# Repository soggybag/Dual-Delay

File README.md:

# Dual Delay (working name)

Two PT2399 delay lines whose repeats can feed themselves, each other, or a blend of both. Idea stage (2026-10-25).

- **Idea and design plan:** [docs/Ideas.md](docs/Ideas.md)
- **Sibling project:** `../Loop Echo/` (single PT2399 + effects loop in the feedback). The delay block, limiter, LFO and mixer are reused from it (its PT2399 network comes from the user's Small Time, 2022).

- **Schematic:** [docs/DualDelay_schematic.pdf](docs/DualDelay_schematic.pdf), generated by `scripts/build_dualdelay.py` (`DualDelay.kicad_sch`). ERC 0. Rev 1.0.
- **Board:** `DualDelay.kicad_pcb`, from `scripts/buildpcb_dualdelay.py` (don't re-run it after editing the board in KiCad).

**Panel (1590BB landscape):** TIME 1, TIME 2, MIX over FB 1, TWIST, FB 2; SERIES toggle; status LED; one footswitch. Internal trims: RATE, DEPTH (LFO on line 2), FB MAX 1 / 2.

**Status:** **v1.0 SMD (2026-10-25)**, to be ordered as a prototype together with Loop Echo (not breadboarded). ERC 0. JLC basic parts except the two PT2399s. One AMS1117-5.0 per PT2399, kept apart on the board; FB MAX trims. Board `DualDelay.kicad_pcb`: 1590BB landscape, 100 × 83.5 mm, jacks on the top wall (OUT · DC · IN). Details: the v1.0 section of [docs/Ideas.md](docs/Ideas.md). **Fab files (2026-10-26, after the re-route):** `production/` (gitignored): `DualDelay.zip` (Gerbers + drill, slots included), `bom.csv` + `positions.csv` (105 SMD placements, top side, 28 lines, all LCSC), `DualDelay_hand_solder.csv`. In JLC's preview check U1 / U2 (PT2399) and U7 / U8 (SOT-223) rotation; the op-amps carry FT Rotation Offset 270. Drilling: [enclosure/README.md](enclosure/README.md). Routed 2026-10-26 (re-route: supply nets +9V / GND / V5_1 / V5_2 / VB / D1-A at 0.4 mm, signals 0.25 mm, 99 vias; C32 GND pad solid). Board DRC: 0 errors / 0 unconnected, parity clean, silk pass done 2026-10-26 (Gerbers regenerated): the only warnings left are the jack outlines past the top edge and D6's LED ring near the notch (by design), and four references touching a part outline (C13, C20, C28, C30). v0.2 breadboard schematic and its [Breadboard Plan](docs/Breadboard%20Plan.md) kept for reference (`scripts/build_dualdelay_v0.2.py`).

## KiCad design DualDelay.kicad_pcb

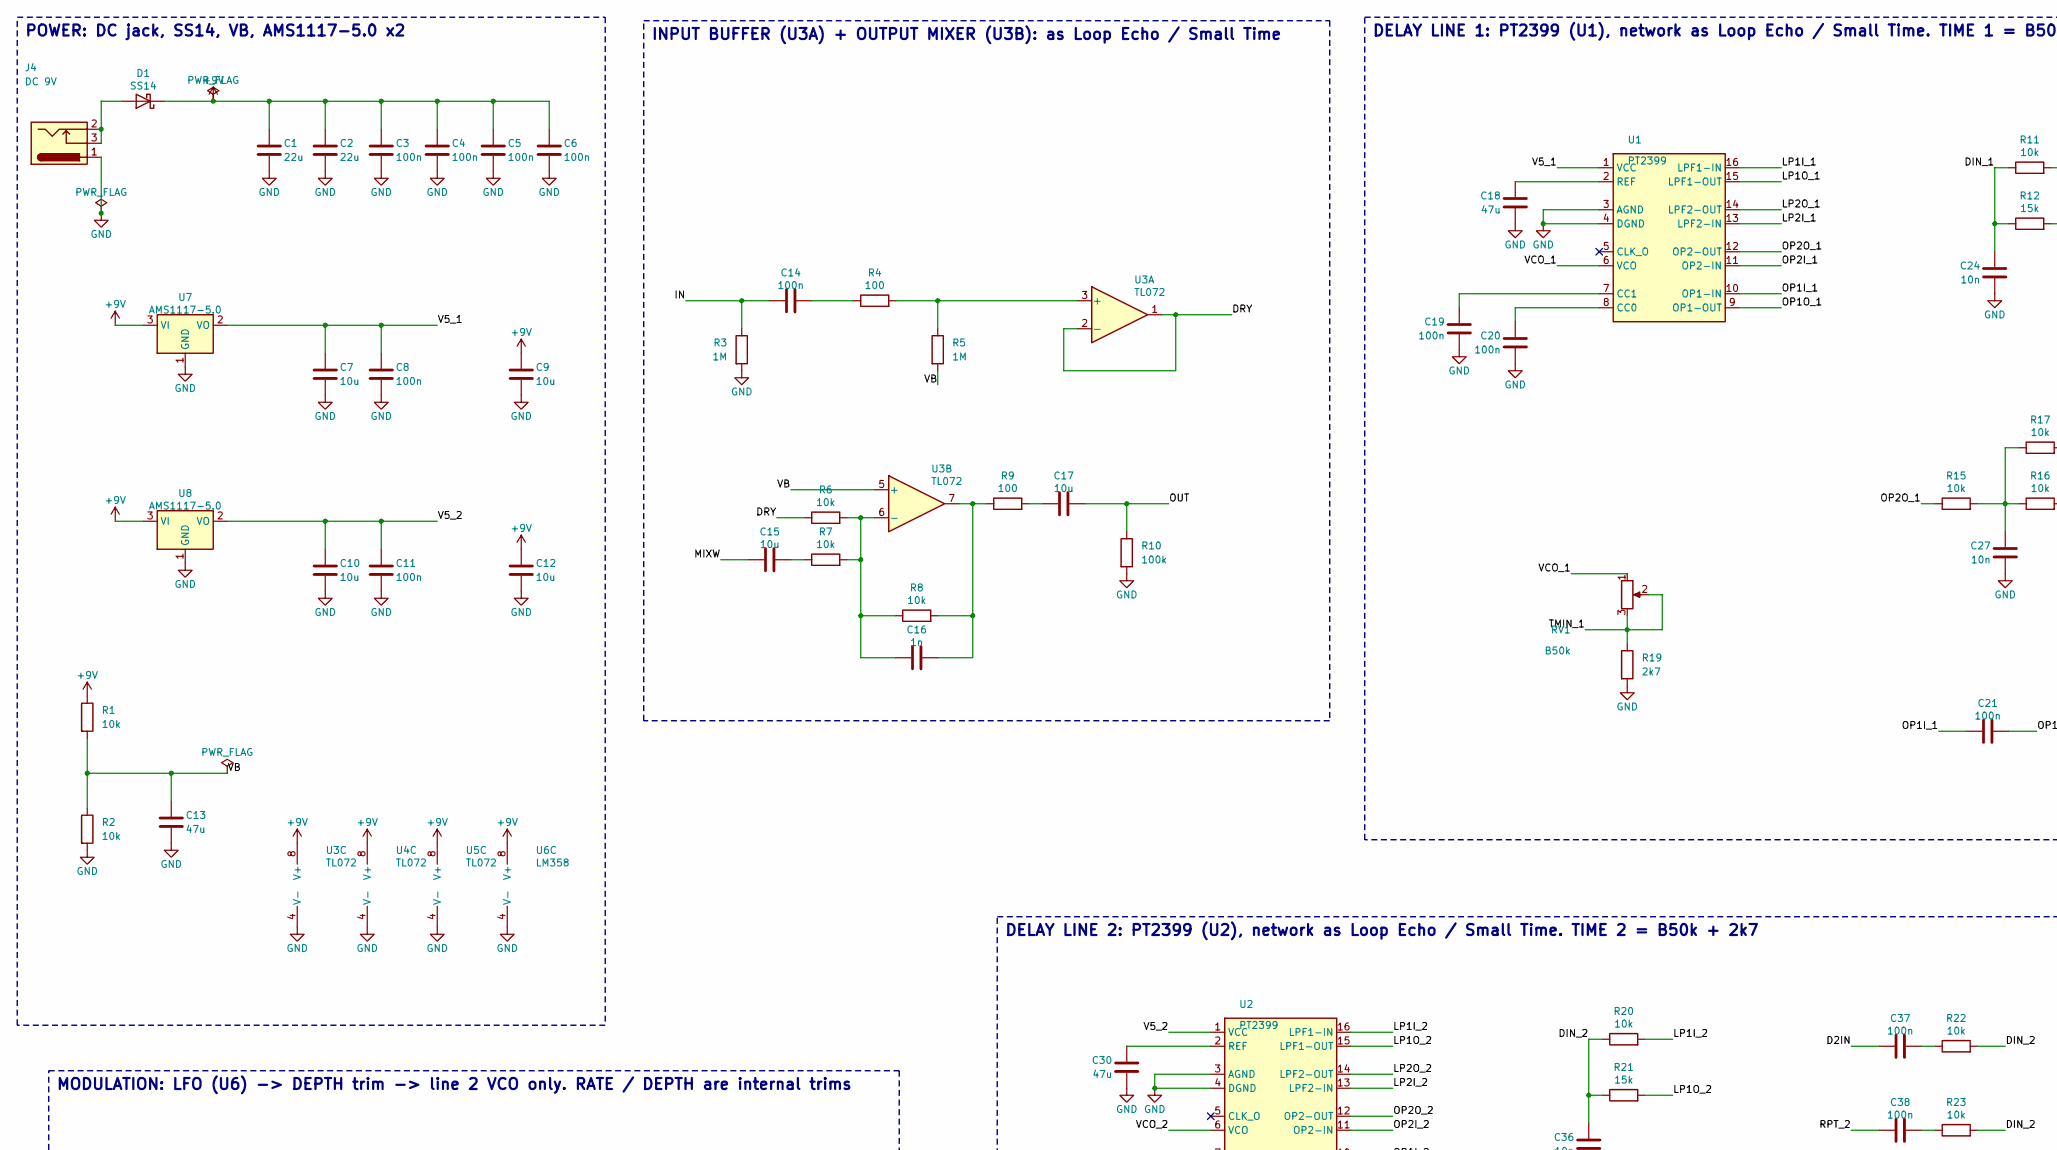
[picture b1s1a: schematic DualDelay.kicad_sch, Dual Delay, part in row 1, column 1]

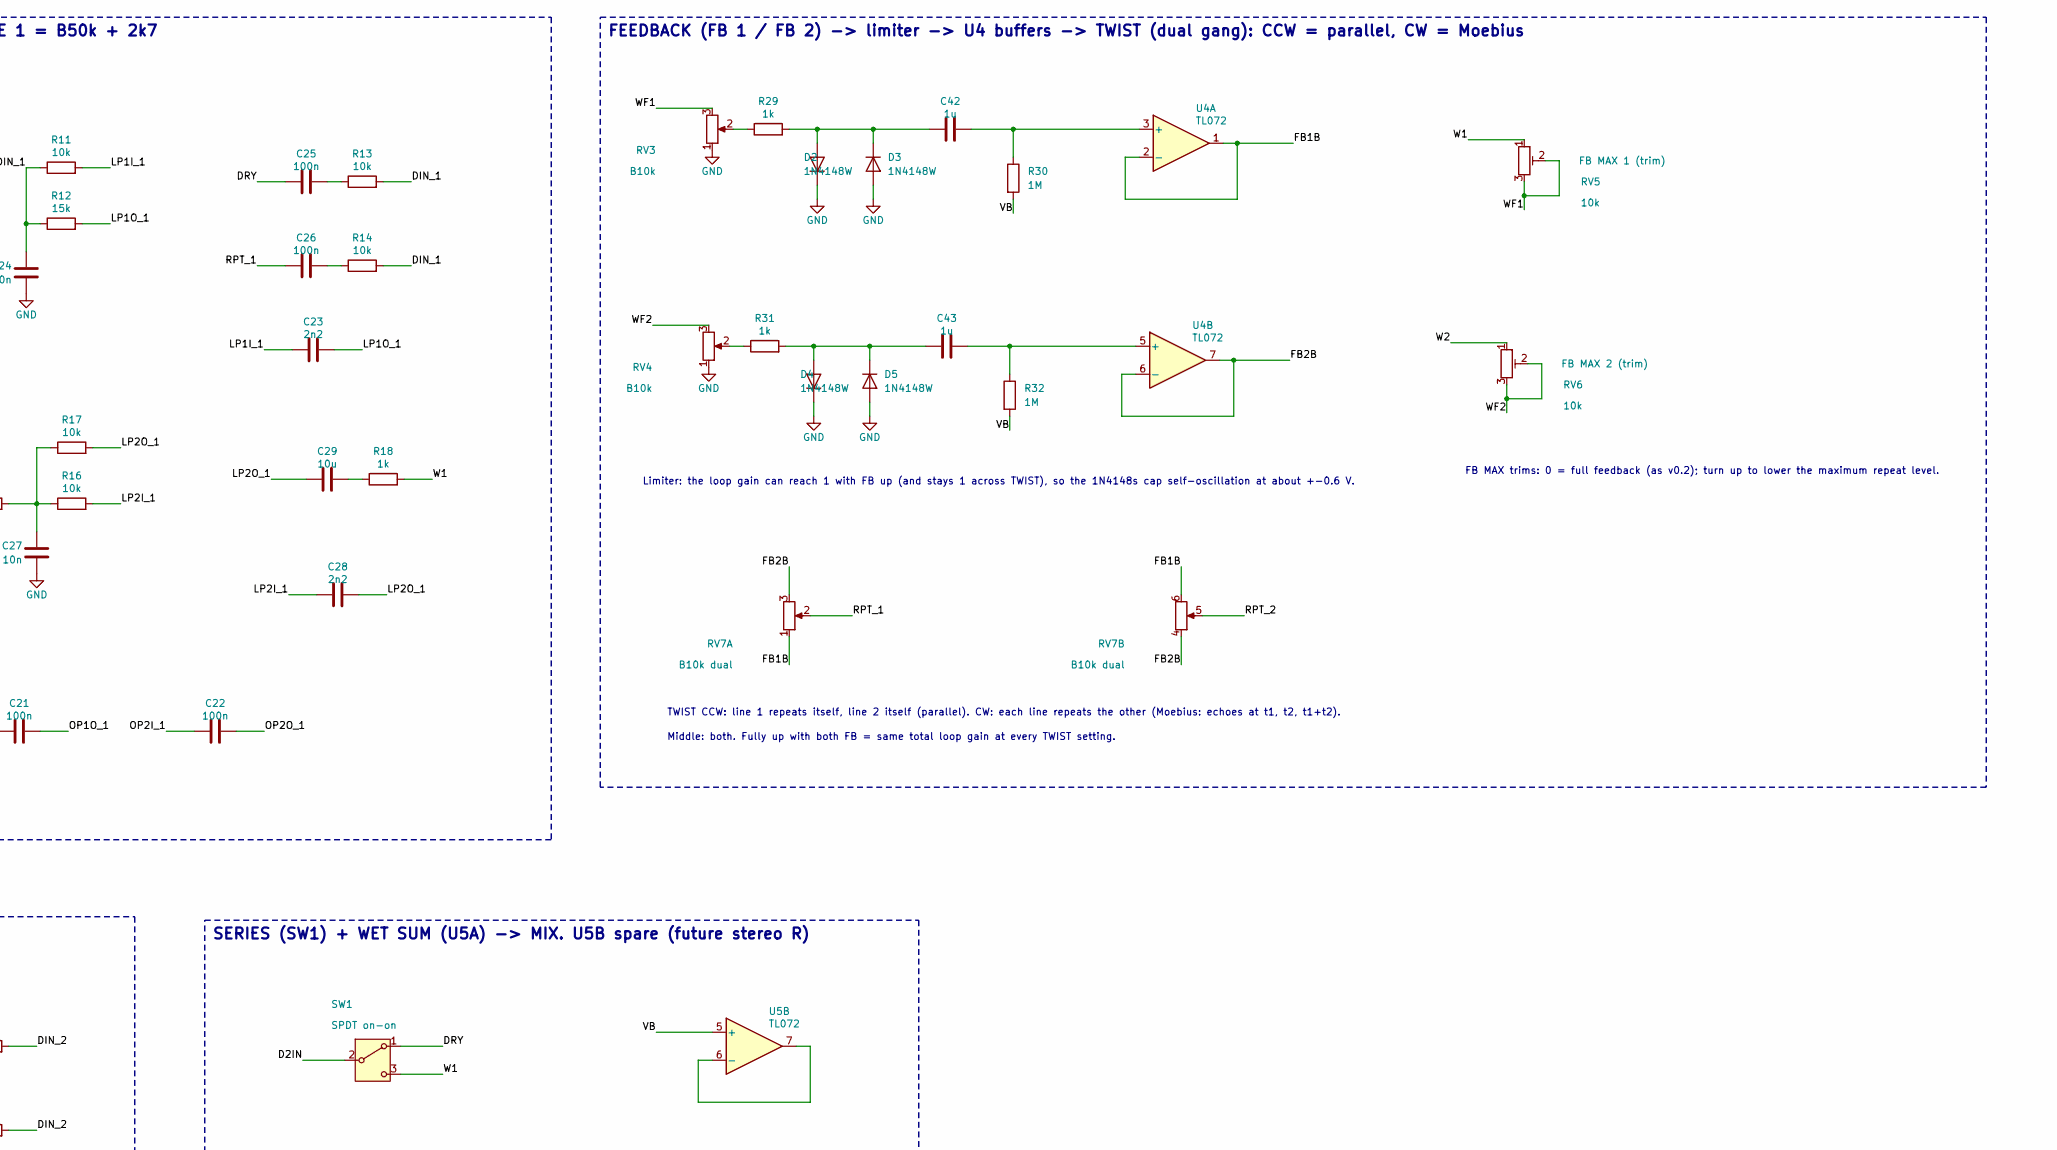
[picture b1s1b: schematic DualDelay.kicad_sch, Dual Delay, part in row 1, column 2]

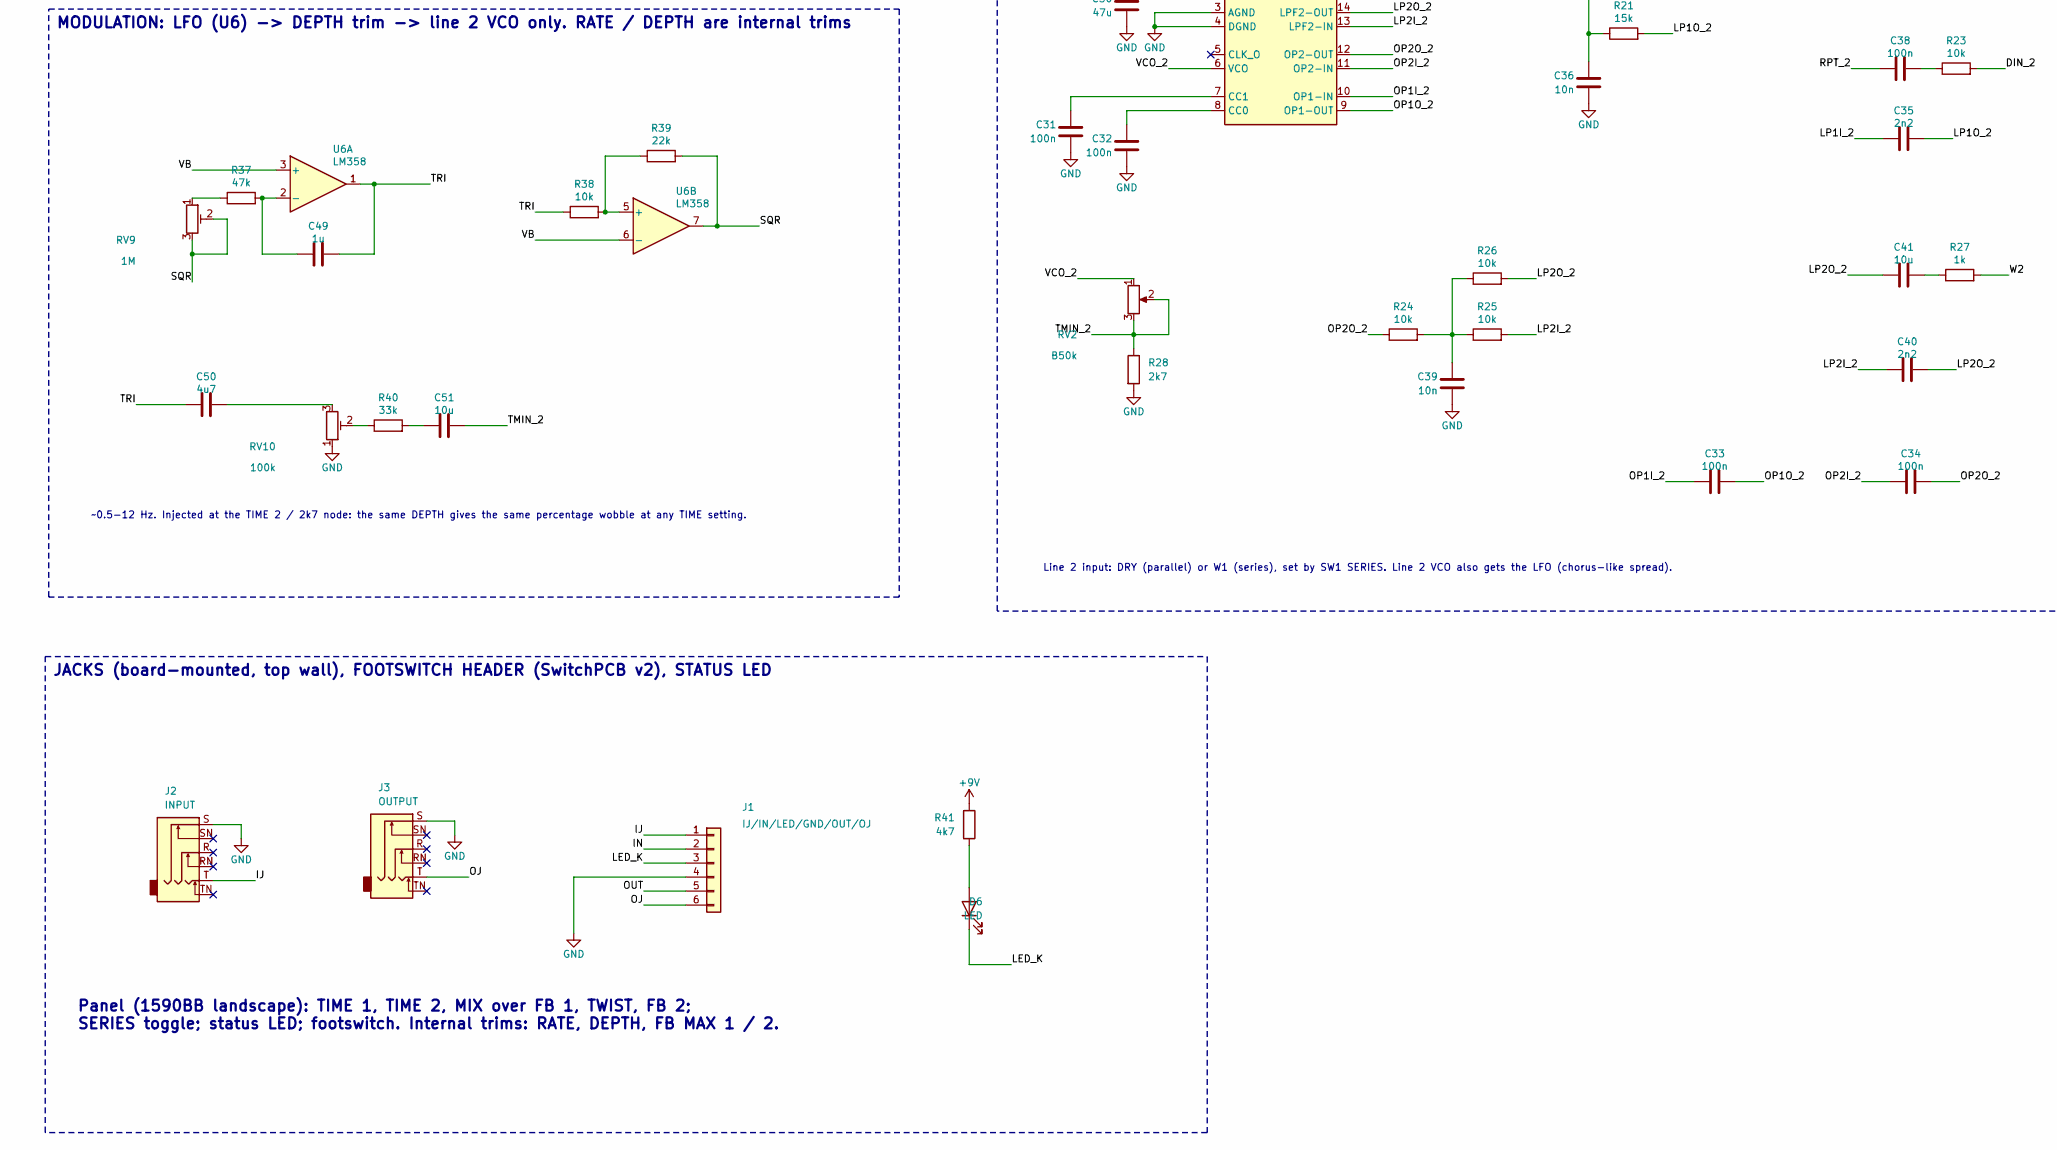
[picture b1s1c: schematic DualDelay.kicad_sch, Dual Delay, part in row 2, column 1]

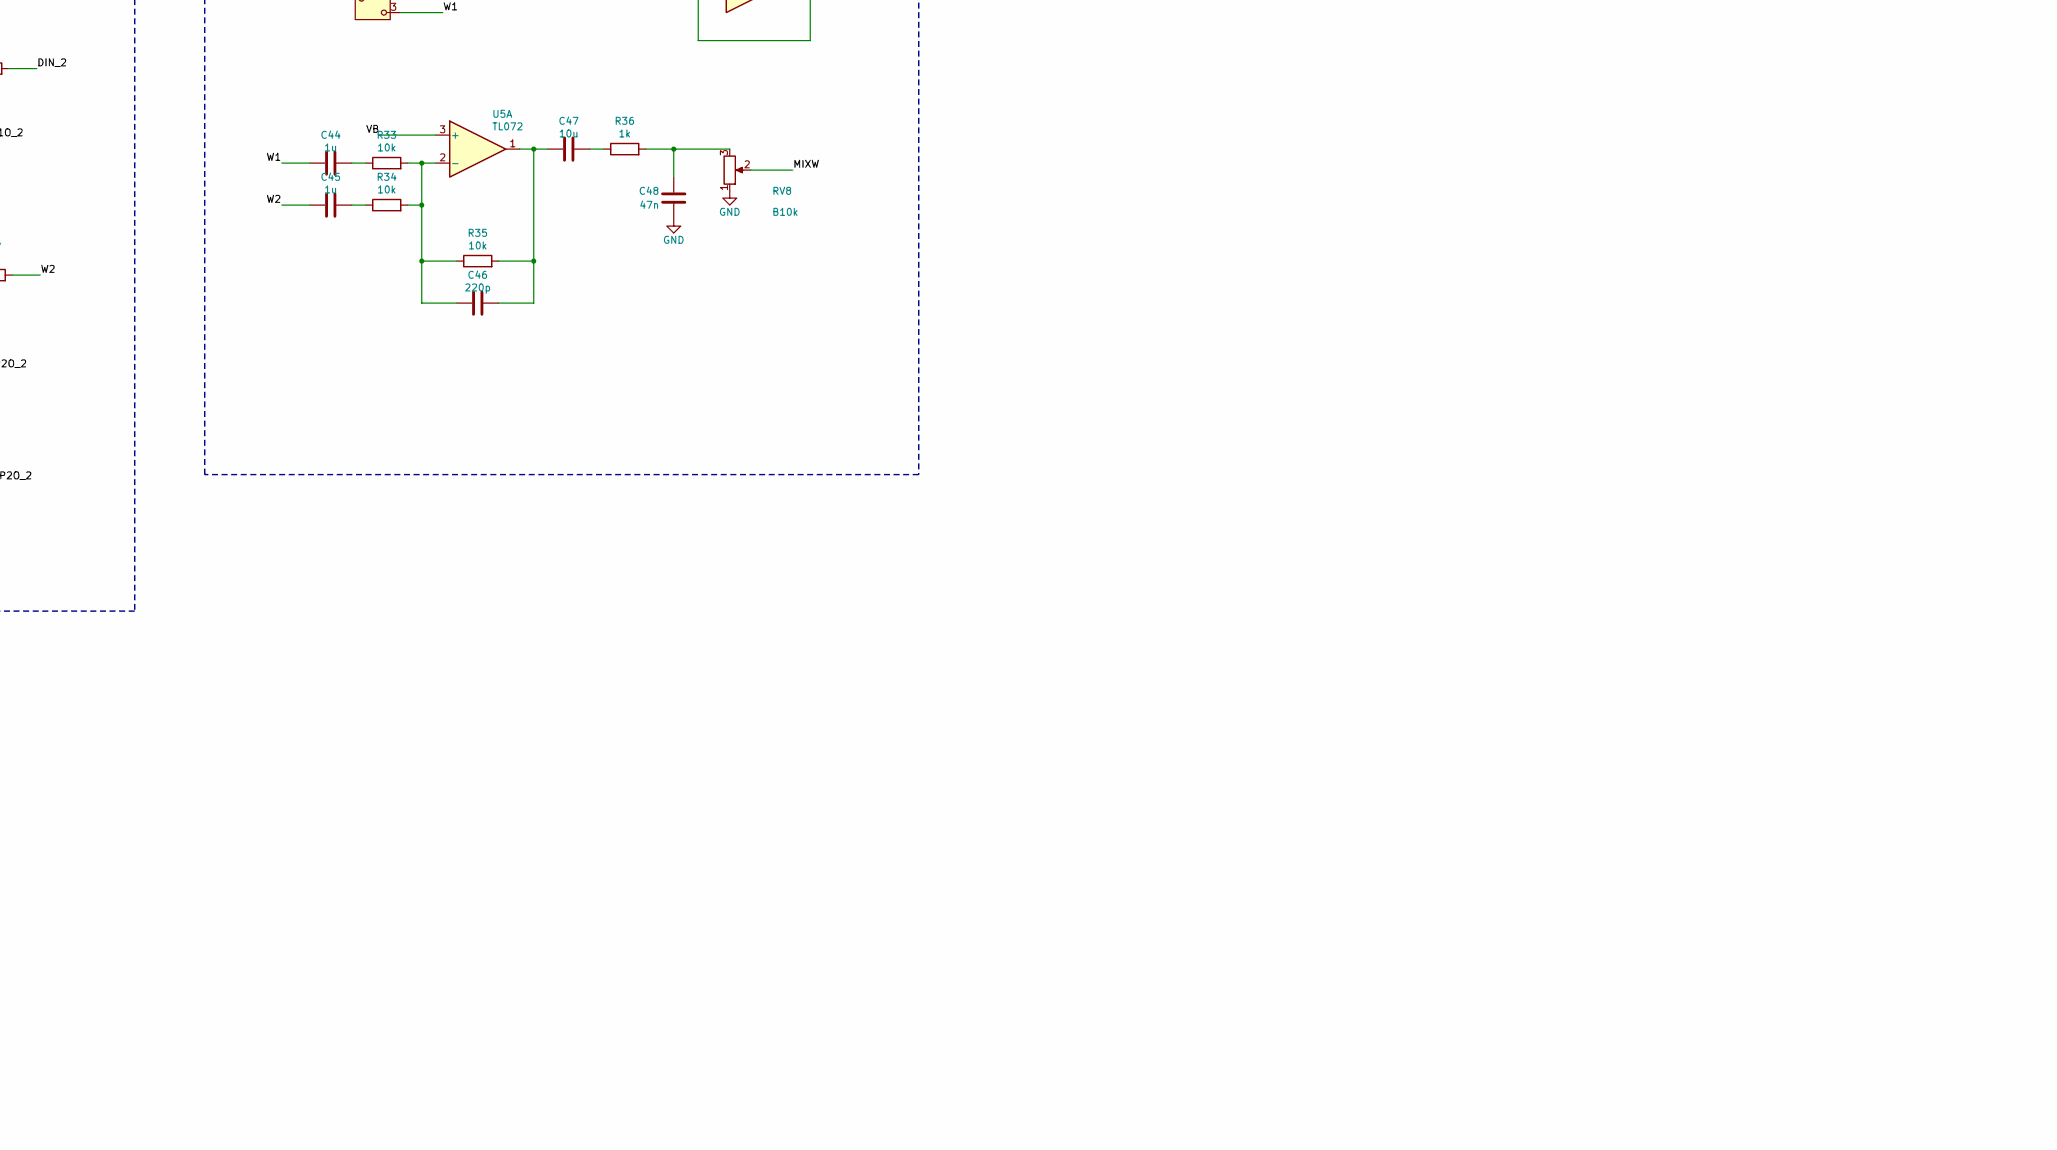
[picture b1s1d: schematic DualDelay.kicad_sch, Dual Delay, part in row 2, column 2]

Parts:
C1, C2: 22u; C_0805_2012Metric_Pad1.18x1.45mm_HandSolder; LCSC C45783
C3, C4, C5, C6, C8, C11, C14, C19, C20, C21, C22, C25, C26, C31, C32, C33, C34, C37, C38: 100n; C_0805_2012Metric_Pad1.18x1.45mm_HandSolder; LCSC C49678
C7, C9, C10, C12, C15, C17, C29, C41, C47, C51: 10u; C_0805_2012Metric_Pad1.18x1.45mm_HandSolder; LCSC C15850
C13, C18, C30: 47u; C_1206_3216Metric_Pad1.33x1.80mm_HandSolder; LCSC C96123
C16: 1n; C_0805_2012Metric_Pad1.18x1.45mm_HandSolder; LCSC C46653
C23, C28, C35, C40: 2n2; C_0805_2012Metric_Pad1.18x1.45mm_HandSolder; LCSC C28260
C24, C27, C36, C39: 10n; C_0805_2012Metric_Pad1.18x1.45mm_HandSolder; LCSC C1710
C42, C43, C44, C45, C49: 1u; C_0805_2012Metric_Pad1.18x1.45mm_HandSolder; LCSC C28323
C46: 220p; C_0805_2012Metric_Pad1.18x1.45mm_HandSolder; LCSC C107145
C48: 47n; C_0805_2012Metric_Pad1.18x1.45mm_HandSolder; LCSC C53134
C50: 4u7; C_0805_2012Metric_Pad1.18x1.45mm_HandSolder; LCSC C1779
D1: SS14; D_SMA; LCSC C2480
D2, D3, D4, D5: 1N4148W; D_SOD-123; LCSC C81598
D6: LED; LED_D3.0mm
J1: IJ/IN/LED/GND/OUT/OJ; PinHeader_1x06_P2.54mm_Vertical
J2: INPUT; Jack_6.35mm_PJ-646F_Horizontal
J3: OUTPUT; Jack_6.35mm_PJ-646F_Horizontal
J4: DC 9V; DC_Jack_2.1mm_A-4118_Horizontal
R1, R2, R6, R7, R8, R11, R13, R14, R15, R16, R17, R20, R22, R23, R24, R25, R26, R33, R34, R35, R38: 10k; R_0805_2012Metric_Pad1.20x1.40mm_HandSolder; LCSC C17414
R3, R5, R30, R32: 1M; R_0805_2012Metric_Pad1.20x1.40mm_HandSolder; LCSC C17514
R4, R9: 100; R_0805_2012Metric_Pad1.20x1.40mm_HandSolder; LCSC C17408
R10: 100k; R_0805_2012Metric_Pad1.20x1.40mm_HandSolder; LCSC C149504
R12, R21: 15k; R_0805_2012Metric_Pad1.20x1.40mm_HandSolder; LCSC C17475
R18, R27, R29, R31, R36: 1k; R_0805_2012Metric_Pad1.20x1.40mm_HandSolder; LCSC C17513
R19, R28: 2k7; R_0805_2012Metric_Pad1.20x1.40mm_HandSolder; LCSC C17530
R37: 47k; R_0805_2012Metric_Pad1.20x1.40mm_HandSolder; LCSC C17713
R39: 22k; R_0805_2012Metric_Pad1.20x1.40mm_HandSolder; LCSC C17560
R40: 33k; R_0805_2012Metric_Pad1.20x1.40mm_HandSolder; LCSC C17633
R41: 4k7; R_0805_2012Metric_Pad1.20x1.40mm_HandSolder; LCSC C17673
RV1, RV2: B50k; Potentiometer_Alpha_RD901F-40-00D_Single_Vertical
RV3, RV4, RV8: B10k; Potentiometer_Alpha_RD901F-40-00D_Single_Vertical
RV5, RV6: 10k; Potentiometer_Bourns_3296W_Vertical
RV7: B10k dual; Potentiometer_9mm_Dual_Vertical_Tayda
RV9: 1M; Potentiometer_Bourns_3296W_Vertical
RV10: 100k; Potentiometer_Bourns_3296W_Vertical
SW1: SPDT on-on; SW_Taiway_100_SPDT_PC
U1, U2: PT2399; SOIC-16_3.9x9.9mm_P1.27mm; LCSC C126407
U3, U4, U5: TL072; SOIC-8_3.9x4.9mm_P1.27mm; LCSC C6961
U6: LM358; SOIC-8_3.9x4.9mm_P1.27mm; LCSC C7950
U7, U8: AMS1117-5.0; SOT-223-3_TabPin2; LCSC C6187

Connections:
/D2IN: C37.1, SW1.2 (B)
/DIN_1: C24.1, R11.1, R12.1, R13.2, R14.2
/DIN_2: C36.1, R20.1, R21.1, R22.2, R23.2
/DRY: C25.1, R6.1, SW1.1 (A), U3.1, U3.2 (-)
/FB1B: RV7.1, RV7.6, U4.1, U4.2 (-)
/FB2B: RV7.3, RV7.4, U4.6 (-), U4.7
/IJ: J1.1, J2.T
/IN: C14.1, J1.2, R3.1
/LED_K: D6.1 (K), J1.3
/LP1I_1: C23.1, R11.2, U1.16 (LPF1-IN)
/LP1I_2: C35.1, R20.2, U2.16 (LPF1-IN)
/LP1O_1: C23.2, R12.2, U1.15 (LPF1-OUT)
/LP1O_2: C35.2, R21.2, U2.15 (LPF1-OUT)
/LP2I_1: C28.1, R16.2, U1.13 (LPF2-IN)
/LP2I_2: C40.1, R25.2, U2.13 (LPF2-IN)
/LP2O_1: C28.2, C29.1, R17.2, U1.14 (LPF2-OUT)
/LP2O_2: C40.2, C41.1, R26.2, U2.14 (LPF2-OUT)
/MIXW: C15.1, RV8.2
/OJ: J1.6, J3.T
/OP1I_1: C21.1, U1.10 (OP1-IN)
/OP1I_2: C33.1, U2.10 (OP1-IN)
/OP1O_1: C21.2, U1.9 (OP1-OUT)
/OP1O_2: C33.2, U2.9 (OP1-OUT)
/OP2I_1: C22.1, U1.11 (OP2-IN)
/OP2I_2: C34.1, U2.11 (OP2-IN)
/OP2O_1: C22.2, R15.1, U1.12 (OP2-OUT)
/OP2O_2: C34.2, R24.1, U2.12 (OP2-OUT)
/OUT: C17.2, J1.5, R10.1
/RPT_1: C26.1, RV7.2
/RPT_2: C38.1, RV7.5
/SQR: R39.2, RV9.2, RV9.3, U6.7
/TMIN_1: R19.1, RV1.2, RV1.3
/TMIN_2: C51.1, R28.1, RV2.2, RV2.3
/TRI: C49.2, C50.1, R38.1, U6.1
/V5_1: C7.1, C8.1, U1.1 (VCC), U7.2 (VO)
/V5_2: C10.1, C11.1, U2.1 (VCC), U8.2 (VO)
/VCO_1: RV1.1, U1.6 (VCO)
/VCO_2: RV2.1, U2.6 (VCO)
/W1: C44.1, R18.2, RV5.1, SW1.3 (C)
/W2: C45.1, R27.2, RV6.1
/WF1: RV3.3, RV5.2, RV5.3
/WF2: RV4.3, RV6.2, RV6.3
unnamed: C14.2, R4.1
unnamed: C15.2, R7.1
unnamed: C16.2, R8.2, R9.1, U3.7
unnamed: C17.1, R9.2
unnamed: C25.2, R13.1
unnamed: C26.2, R14.1
unnamed: C27.1, R15.2, R16.1, R17.1
unnamed: C29.2, R18.1
unnamed: C37.2, R22.1
unnamed: C38.2, R23.1
unnamed: C39.1, R24.2, R25.1, R26.1
unnamed: C41.2, R27.1
unnamed: C44.2, R33.1
unnamed: C45.2, R34.1
unnamed: C46.2, C47.1, R35.2, U5.1
unnamed: C47.2, R36.1
unnamed: C48.1, R36.2, RV8.3
unnamed: C50.2, RV10.3
unnamed: C51.2, R40.2
unnamed: D1.2 (A), J4.2, J4.3
unnamed: C42.1, D2.2 (A), D3.1 (K), R29.2
unnamed: C43.1, D4.2 (A), D5.1 (K), R31.2
unnamed: D6.2 (A), R41.2
unnamed: R29.1, RV3.2
unnamed: R31.1, RV4.2
unnamed: R37.1, RV9.1
unnamed: R40.1, RV10.2
unnamed: C20.1, U1.8 (CC0)
unnamed: C19.1, U1.7 (CC1)
unnamed: C18.1, U1.2 (REF)
unnamed: C32.1, U2.8 (CC0)
unnamed: C31.1, U2.7 (CC1)
unnamed: C30.1, U2.2 (REF)
unnamed: R4.2, R5.1, U3.3 (+)
unnamed: C16.1, R6.2, R7.2, R8.1, U3.6 (-)
unnamed: C42.2, R30.1, U4.3 (+)
unnamed: C43.2, R32.1, U4.5 (+)
unnamed: C46.1, R33.2, R34.2, R35.1, U5.2 (-)
unnamed: U5.6 (-), U5.7
unnamed: C49.1, R37.2, U6.2 (-)
unnamed: R38.2, R39.1, U6.5 (+)

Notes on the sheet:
DELAY LINE 2: PT2399 (U2), network as Loop Echo / Small Time. TIME 2 = B50k + 2k7
MODULATION: LFO (U6) -> DEPTH trim -> line 2 VCO only. RATE / DEPTH are internal trims
~0.5-12 Hz. Injected at the TIME 2 / 2k7 node: the same DEPTH gives the same percentage wobble at any TIME setting.
Limiter: the loop gain can reach 1 with FB up (and stays 1 across TWIST), so the 1N4148s cap self-oscillation at about +-0.6 V.
TWIST CCW: line 1 repeats itself, line 2 itself (parallel). CW: each line repeats the other (Moebius: echoes at t1, t2, t1+t2).
SERIES (SW1) + WET SUM (U5A) -> MIX. U5B spare (future stereo R)
INPUT BUFFER (U3A) + OUTPUT MIXER (U3B): as Loop Echo / Small Time
POWER: DC jack, SS14, VB, AMS1117-5.0 x2
Line 2 input: DRY (parallel) or W1 (series), set by SW1 SERIES. Line 2 VCO also gets the LFO (chorus-like spread).
Panel (1590BB landscape): TIME 1, TIME 2, MIX over FB 1, TWIST, FB 2; SERIES toggle; status LED; footswitch. Internal trims: RATE, DEPTH, FB MAX 1 / 2.
Middle: both. Fully up with both FB = same total loop gain at every TWIST setting.
FB MAX trims: 0 = full feedback (as v0.2); turn up to lower the maximum repeat level.
FEEDBACK (FB 1 / FB 2) -> limiter -> U4 buffers -> TWIST (dual gang): CCW = parallel, CW = Moebius
JACKS (board-mounted, top wall), FOOTSWITCH HEADER (SwitchPCB v2), STATUS LED
DELAY LINE 1: PT2399 (U1), network as Loop Echo / Small Time. TIME 1 = B50k + 2k7

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
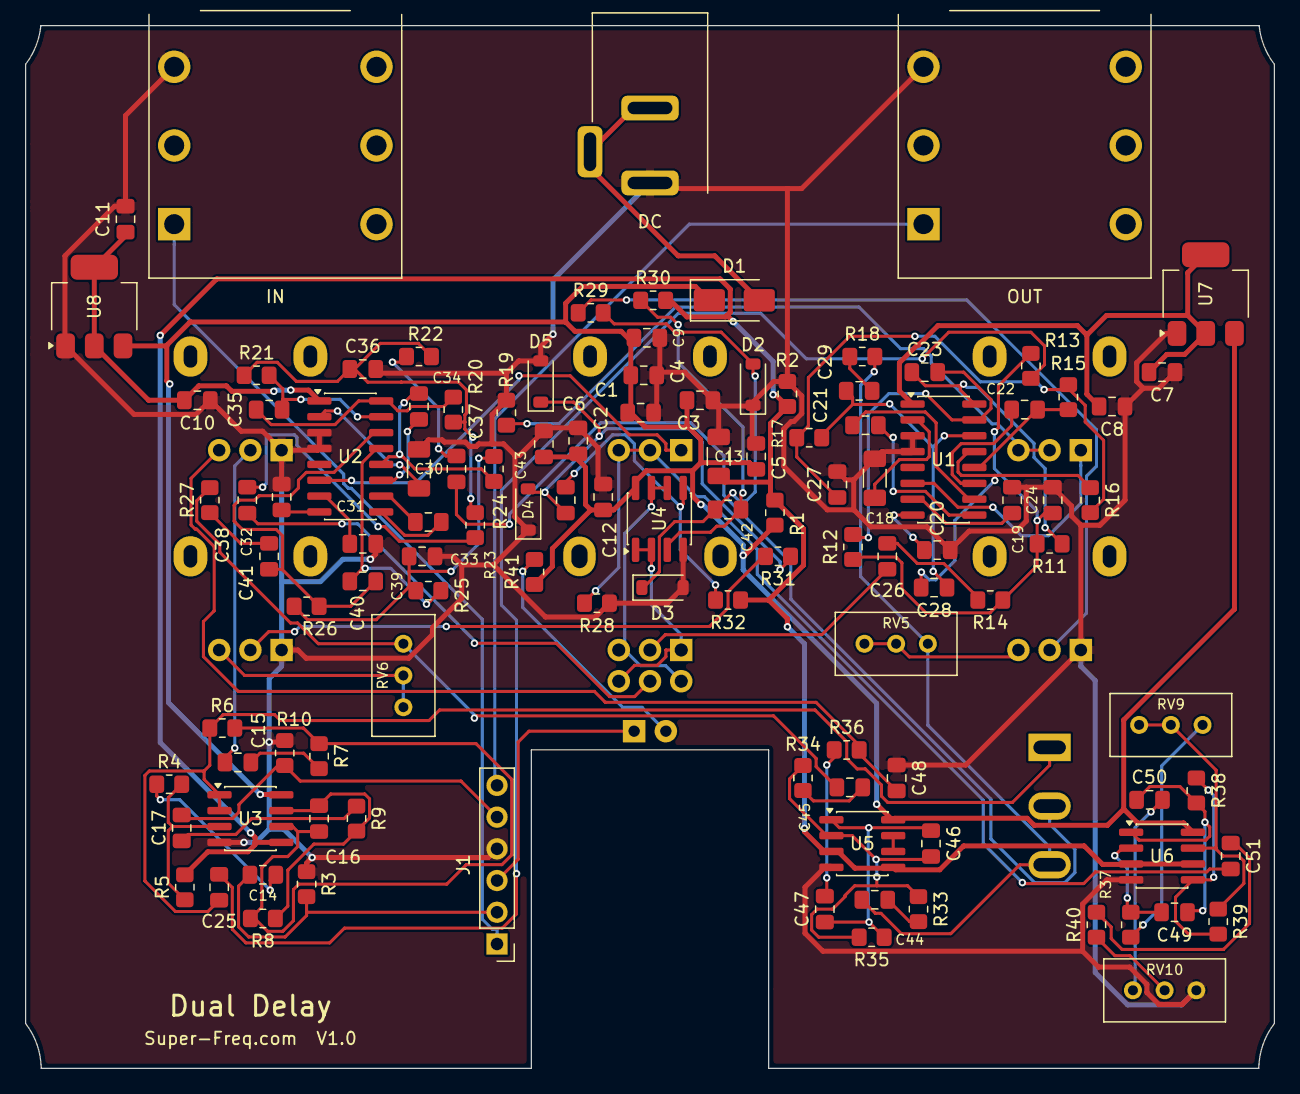
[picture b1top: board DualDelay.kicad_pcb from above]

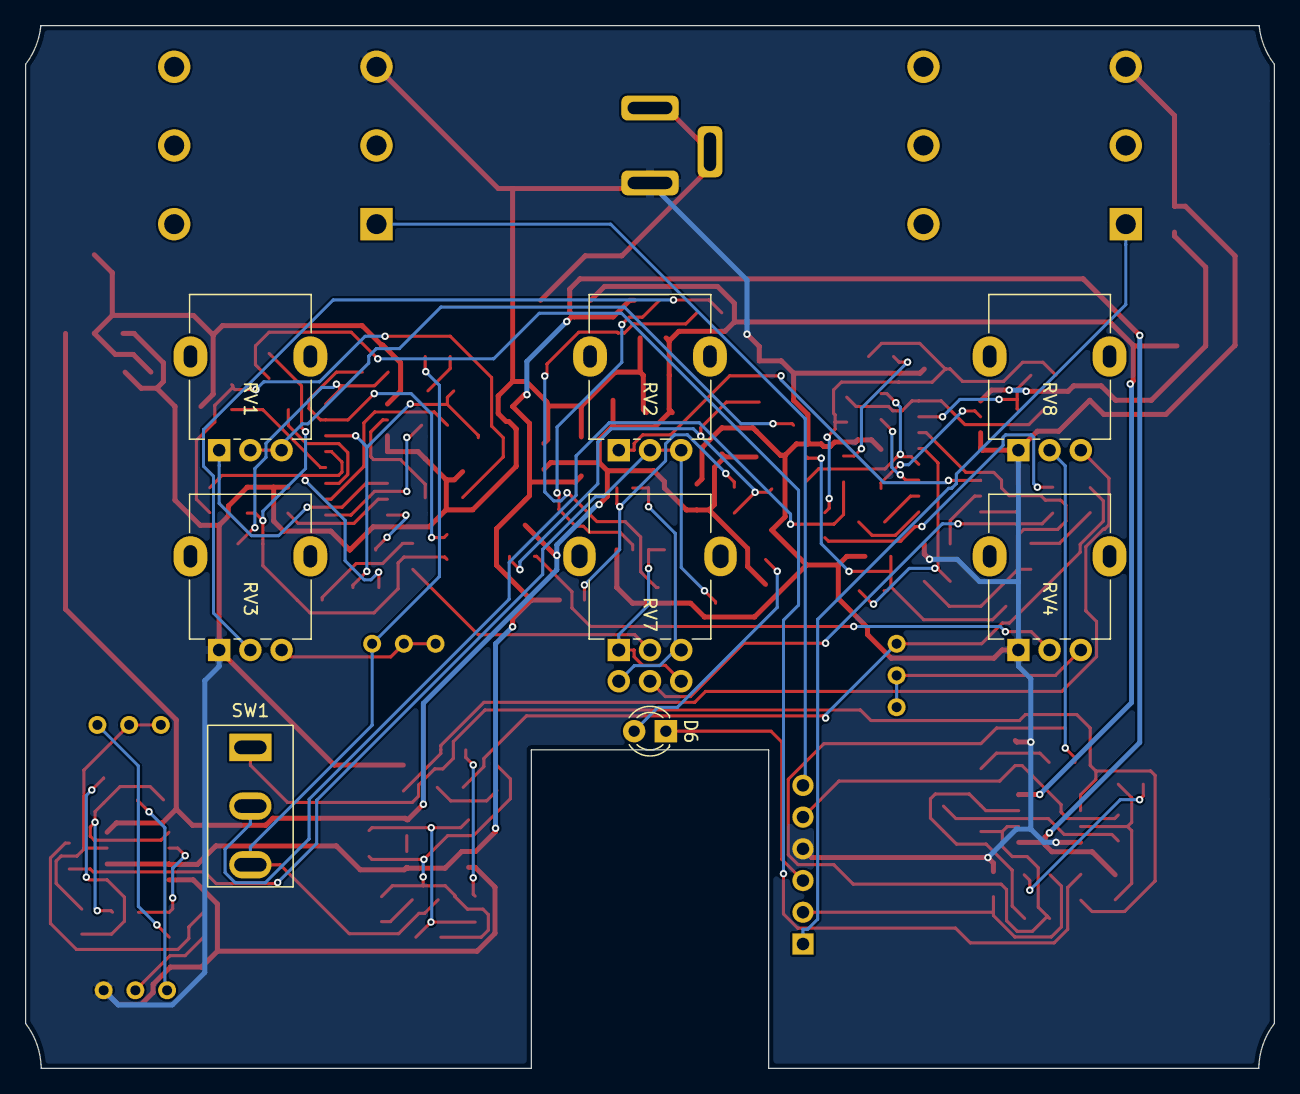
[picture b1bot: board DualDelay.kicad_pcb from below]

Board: 2 copper layers, 100.0 x 83.5 mm, 121 parts (8 on the bottom side), 86 nets.

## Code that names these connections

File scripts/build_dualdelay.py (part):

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s.text('FB MAX trims: 0 = full feedback (as v0.2); turn up to lower the maximum repeat level.', g(330), g(60))
s.text('Limiter: the loop gain can reach 1 with FB up (and stays 1 across TWIST), so the 1N4148s cap self-oscillation at about +-0.6 V.', g(256), g(68))
TW = nx('RV')
# TWIST: gang A pin 1 (CCW) = FB1B, pin 3 (CW) = FB2B, wiper = RPT_1; gang B pin 4 (CCW) = FB2B, pin 6 (CW) = FB1B, wiper = RPT_2
s.part(TW, 'Device', 'R_Potentiometer_Dual_Separate', 'B10k dual', g(272), g(86), 0, unit=1, mirror='x', fp=FDUAL, bom=False, desc='TWIST (dual gang)',
       extra={'Panel': 'TWIST'}, text=((g(268), g(88)), (g(268), g(89.5)), 'right'))
s.part(TW, 'Device', 'R_Potentiometer_Dual_Separate', 'B10k dual', g(300), g(86), 0, unit=2, mirror='x', fp=FDUAL, bom=False, desc='TWIST (dual gang)',
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    q = P(ref, 'S'); W(q, (q[0] + g(2), q[1])); gnd_down((q[0] + g(2), q[1]), 1)
s.part('J1', 'Connector_Generic', 'Conn_01x06', 'IJ/IN/LED/GND/OUT/OJ', g(66), g(178), 0, fp='Connector_PinHeader_2.54mm:PinHeader_1x06_P2.54mm_Vertical',
       desc='To the SwitchPCB v2 (same order as its pads): 1 IJ, 2 IN, 3 LED_K, 4 GND, 5 OUT, 6 OJ', text=((g(68), g(174)), (g(68), g(175.2)), 'left'), bom=False)
for pin, net in (('1', 'IJ'), ('2', 'IN'), ('3', 'LED_K'), ('5', 'OUT'), ('6', 'OJ')):
    q = P('J1', pin); W(q, (q[0] - g(3), q[1])); lab(net, (q[0] - g(3), q[1]), 'l')
q = P('J1', '4'); W(q, (q[0] - g(8), q[1]), (q[0] - g(8), q[1] + g(4))); GND((q[0] - g(8), q[1] + g(4)))
r = Rv('4k7', g(96), g(170), side='l', d='Status LED current'); V9(P(r, '1'))
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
